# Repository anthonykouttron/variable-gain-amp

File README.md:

# variable-gain-amp
Custom Analog Amplifier KiCad Design Challenge

The challenge question in full:

My Approach:

I designed a variable analog amplifier circuit with adjustable gain in KiCad 4.0.6
An adjustable gain was implemented using a potentiometer and a variable capacitor bank was used to allow for fine adjustment of the cut-off frequency of the low pass filter. I used a traditional barrel jack for 5v imput power and two simple terminal blocks for input and output waveforms.

My circuit successfully takes an input analog signal between 0-2V and produces an output voltage between 0-5V.
The schematic has been tested with TINA-TI Spice and it passed DRC without any errors. I have included bode plots which show the gain changing with frequency and demonstrate low pass filtering.

Top view photo of the layout implemented in Pcbnew:

Bottom view photo of the layout implemented in Pcbnew:

Files included:  
  - Circuit Schematic PDF   
  - BOM   
  - GERBER Files    
  - Drill File    
  - Layout PDF  
  - Images of the PCB 
  - Bode Plots
  - 3D renders

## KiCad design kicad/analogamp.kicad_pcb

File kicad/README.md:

# variable-gain-amp

The challenge question in full:

My Approach:

I designed a variable analog amplifier circuit with adjustable gain in KiCad 4.0.6
An adjustable gain was implemented using a potentiometer and a variable capacitor bank was used to allow for fine adjustment of the cut-off frequency of the low pass filter. I used a traditional barrel jack for 5v imput power and two simple terminal blocks for input and output waveforms.

My circuit successfully takes an input analog signal between 0-2V and produces an output voltage between 0-5V.
The schematic has been tested with TINA-TI Spice and it passed DRC without any errors. I have included bode plots which show the gain changing with frequency and demonstrate low pass filtering.

Here's a photo of the layout from the top view of the board implemented in Pcbnew:

Here's a photo of the layout from the bottom view of the board implemented in Pcbnew:

More renders are available in the render directory.

Files included:  
Circuit Schematic PDF   
BOM   
GERBER Files    
Drill File    
Layout PDF  
Images of the PCB 
Bode Plots
3D renders

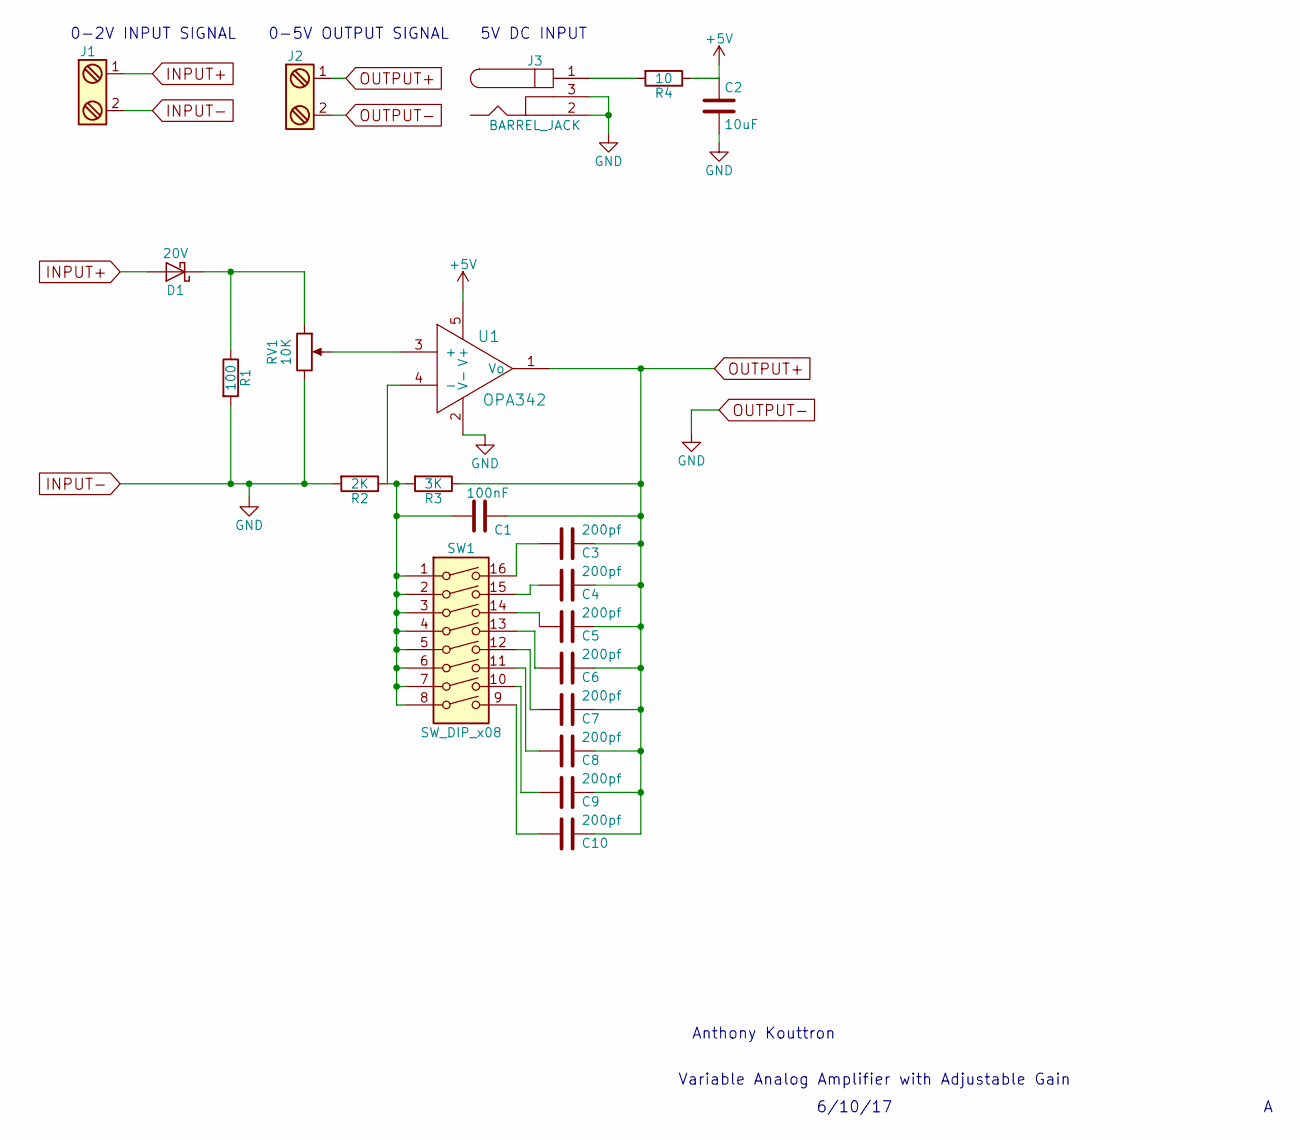
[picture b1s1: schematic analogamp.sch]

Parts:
C1: 100nF; C_0805_HandSoldering
C2: 10uF; C_0805_HandSoldering
C3, C4, C5, C6, C7, C8, C9, C10: 200pf; C_0805_HandSoldering
D1: 20V; D_0805
J1, J2: Screw_Terminal_1x02; TerminalBlock_Pheonix_MKDS1.5-2pol
J3: BARREL_JACK
R1: 100; R_0805_HandSoldering
R2: 2K; R_0805_HandSoldering
R3: 3K; R_0805_HandSoldering
R4: 10; R_0805_HandSoldering
RV1: 10K; Potentiometer_Triwood_RM-065
SW1: SW_DIP_x08; SW_DIP_x8_W7.62mm_Slide_Copal_CHS-B
U1: OPA342; TSOT-23-5_HandSoldering

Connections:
+5V: C2.1, R4.1, U1.5 (V+)
INPUT+: D1.2 (A), J1.1
INPUT-: C2.2, J1.2, J2.2, J3.2, J3.3, R1.2, R2.2, RV1.3, U1.2 (V-)
unnamed: C1.2, R2.1, R3.2, SW1.1, SW1.2, SW1.3, SW1.4, SW1.5, SW1.6, SW1.7, SW1.8, U1.4 (-)
unnamed: C3.2, SW1.16
unnamed: C4.2, SW1.15
unnamed: C5.2, SW1.14
unnamed: C6.2, SW1.13
unnamed: C7.2, SW1.12
unnamed: C8.2, SW1.11
unnamed: C9.2, SW1.10
unnamed: C10.2, SW1.9
unnamed: D1.1 (K), R1.1, RV1.1
unnamed: J3.1, R4.2
unnamed: RV1.2, U1.3 (+)
OUTPUT+: C1.1, C3.1, C4.1, C5.1, C6.1, C7.1, C8.1, C9.1, C10.1, J2.1, R3.1, U1.1 (Vo)

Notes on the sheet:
0-2V INPUT SIGNAL
0-5V OUTPUT SIGNAL
5V DC INPUT
Variable Analog Amplifier with Adjustable Gain
6/10/17
Anthony Kouttron

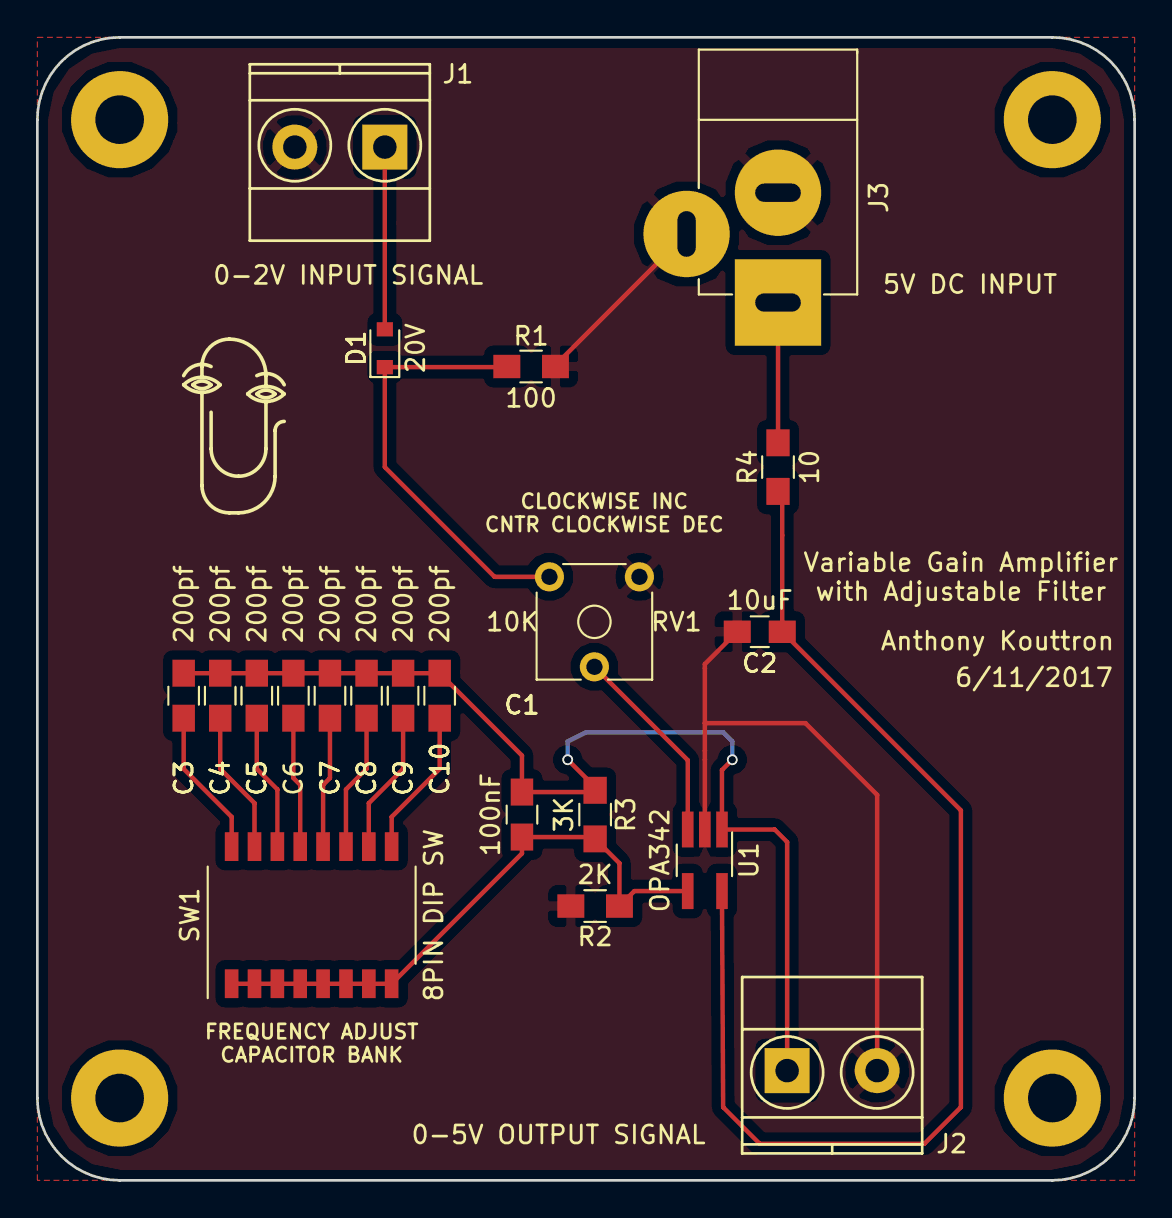
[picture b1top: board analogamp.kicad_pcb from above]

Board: 2 copper layers, 61.0 x 63.5 mm, 21 parts (0 on the bottom side), 16 nets.

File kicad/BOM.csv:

Id,Designator,Package,Quantity,Designation,Supplier and ref
1,C1,C_0805_HandSoldering,1,100nF,https://www.digikey.com/product-detail/en/avx-corporation/08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
2,C2,C_0805_HandSoldering,1,10uF,https://www.digikey.com/product-detail/en/kemet/C0805C106K8P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
3,"C3,C4,C5,C6,C7,C8,C8,C9,C10",C_0805_HandSoldering,8,200pF,https://www.digikey.com/product-detail/en/samsung-electro-me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
4,D1,Diodes_SMD_0805,1,20v,https://www.digikey.com/product-detail/en/avx-corporation/SD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
5,"J1,J2",Pin_Header_Straight_1x02,2,1985865,https://www.digikey.com/products/en?keywords=phoenix%201985865
6,J3,MountingHole_3mm MountingHole_3.5mm,1,PJ-037B,https://www.digikey.com/product-detail/en/cui-inc/PJ-002A/CP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
7,R1,R_0805_HandSoldering,1,100ohm,https://www.digikey.com/product-detail/en/panasonic-electron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
8,R2,R_0805_HandSoldering,1,2K,https://www.digikey.com/product-detail/en/panasonic-electron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
9,R3,R_0805_HandSoldering,1,3K,https://www.digikey.com/product-detail/en/stackpole-electron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
10,R4,R_0805_HandSoldering,1,10ohm,https://www.digikey.com/product-detail/en/panasonic-electron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
11,RV1,Potentiometer_Trimmer_ACP_CA6v_Horizontal,1,10K,https://www.digikey.com/product-detail/en/bourns-inc/3386F-1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
12,SW1,SW_DIP_x08_W7.62mm_Slide_Copal_CHS-B,1,CHS-08TB,https://www.digikey.com/product-detail/en/nidec-copal-electr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
13,U1,SOT23-5,1,OPA342,https://www.digikey.com/product-detail/en/texas-instruments/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
